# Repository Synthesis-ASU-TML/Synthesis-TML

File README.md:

Synthesis
=========

TML members share golden cutting edge paradigm shifting crisp optimized wonderful code with select lucky fellas at the synthesis center at asu arizona.

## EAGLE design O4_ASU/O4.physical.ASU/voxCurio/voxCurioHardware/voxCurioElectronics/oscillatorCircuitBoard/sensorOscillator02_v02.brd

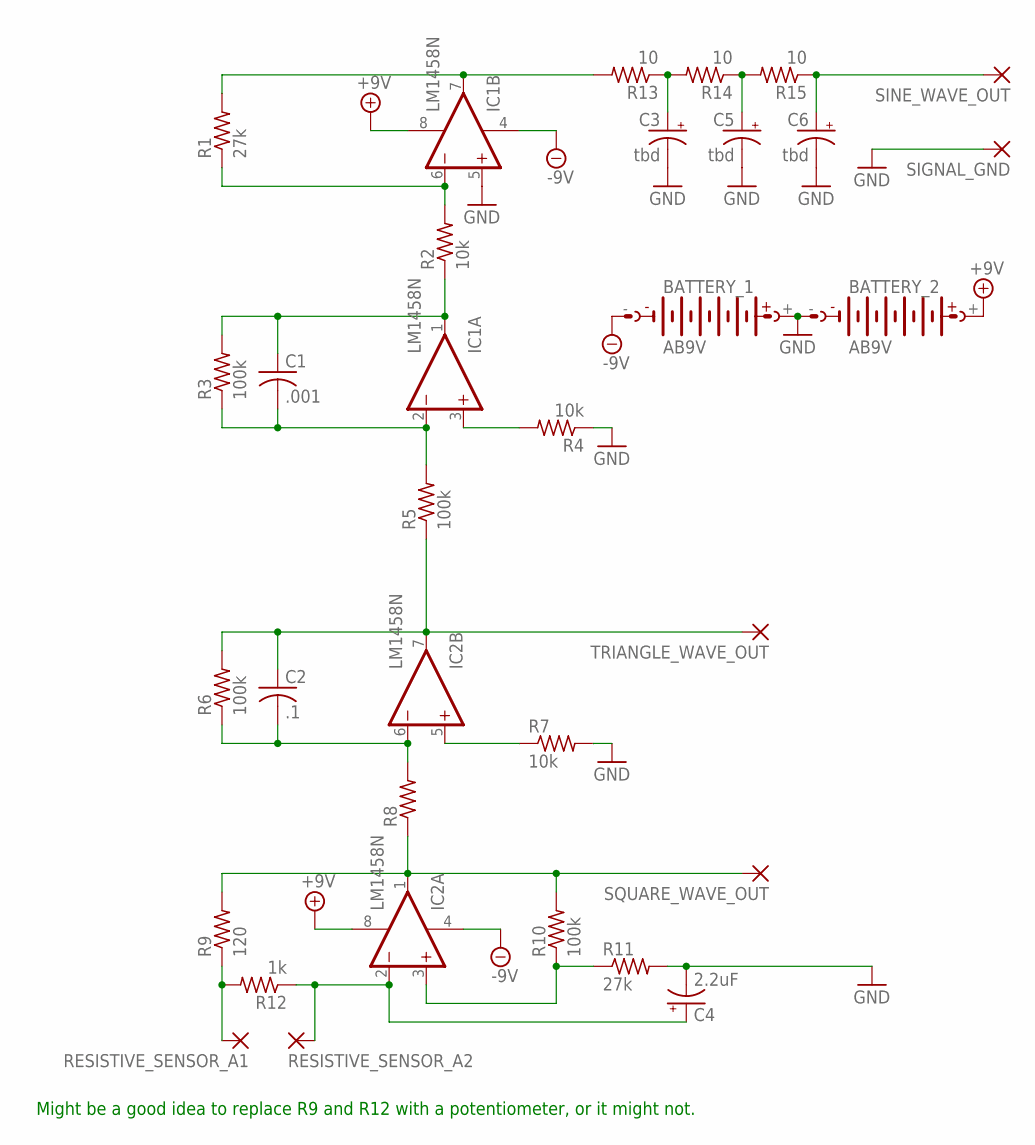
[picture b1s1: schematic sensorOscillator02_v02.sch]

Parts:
BATTERY_1, BATTERY_2: AB9V
C1: .001; C075-063X106
C2: .1; C075-063X106
C3, C5, C6: tbd; E5-5
C4: 2.2uF; E5-5
IC1, IC2: LM1458N; DIL08
R1, R11: 27k; 0411/12
R2, R4, R7: 10k; 0411/12
R3, R5, R6, R10: 100k; 0411/12
R8: R-US_0411/12; 0411/12
R9: 120; 0411/12
R12: 1k; 0411/12
R13, R14, R15: 10; 0411/12
RESISTIVE_SENSOR_A1, RESISTIVE_SENSOR_A2: 3,81/1,3
SIGNAL_GND: 3,81/1,3
SINE_WAVE_OUT: 3,81/1,3
SQUARE_WAVE_OUT: 3,81/1,3
TRIANGLE_WAVE_OUT: 3,81/1,3

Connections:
+9V: BATTERY_2.+, IC1.8 (V+), IC2.8 (V+)
-9V: BATTERY_1.-, IC1.4 (V-), IC2.4 (V-)
GND: BATTERY_1.+, BATTERY_2.-, C3.-, C4.-, C5.-, C6.-, IC1.5 (+IN), R4.1, R7.2, R11.2, SIGNAL_GND.1
unnamed: IC1.6 (-IN), R1.1, R2.2
unnamed: C1.1, IC1.1 (OUT), R2.1, R3.2
unnamed: IC1.7 (OUT), R1.2, R13.2
unnamed: C1.2, IC1.2 (-IN), R3.1, R5.2
unnamed: IC1.3 (+IN), R4.2
unnamed: C2.1, IC2.7 (OUT), R5.1, R6.2, TRIANGLE_WAVE_OUT.1
unnamed: C2.2, IC2.6 (-IN), R6.1, R8.2
unnamed: C3.+, R13.1, R14.2
unnamed: IC2.1 (OUT), R8.1, R9.2, R10.2, SQUARE_WAVE_OUT.1
unnamed: IC2.3 (+IN), R10.1, R11.1
unnamed: R9.1, R12.2, RESISTIVE_SENSOR_A1.1
unnamed: C4.+, IC2.2 (-IN), R12.1, RESISTIVE_SENSOR_A2.1
unnamed: IC2.5 (+IN), R7.1
unnamed: C5.+, R14.1, R15.2
unnamed: C6.+, R15.1, SINE_WAVE_OUT.1

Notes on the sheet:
Might be a good idea to replace R9 and R12 with a potentiometer, or it might not.

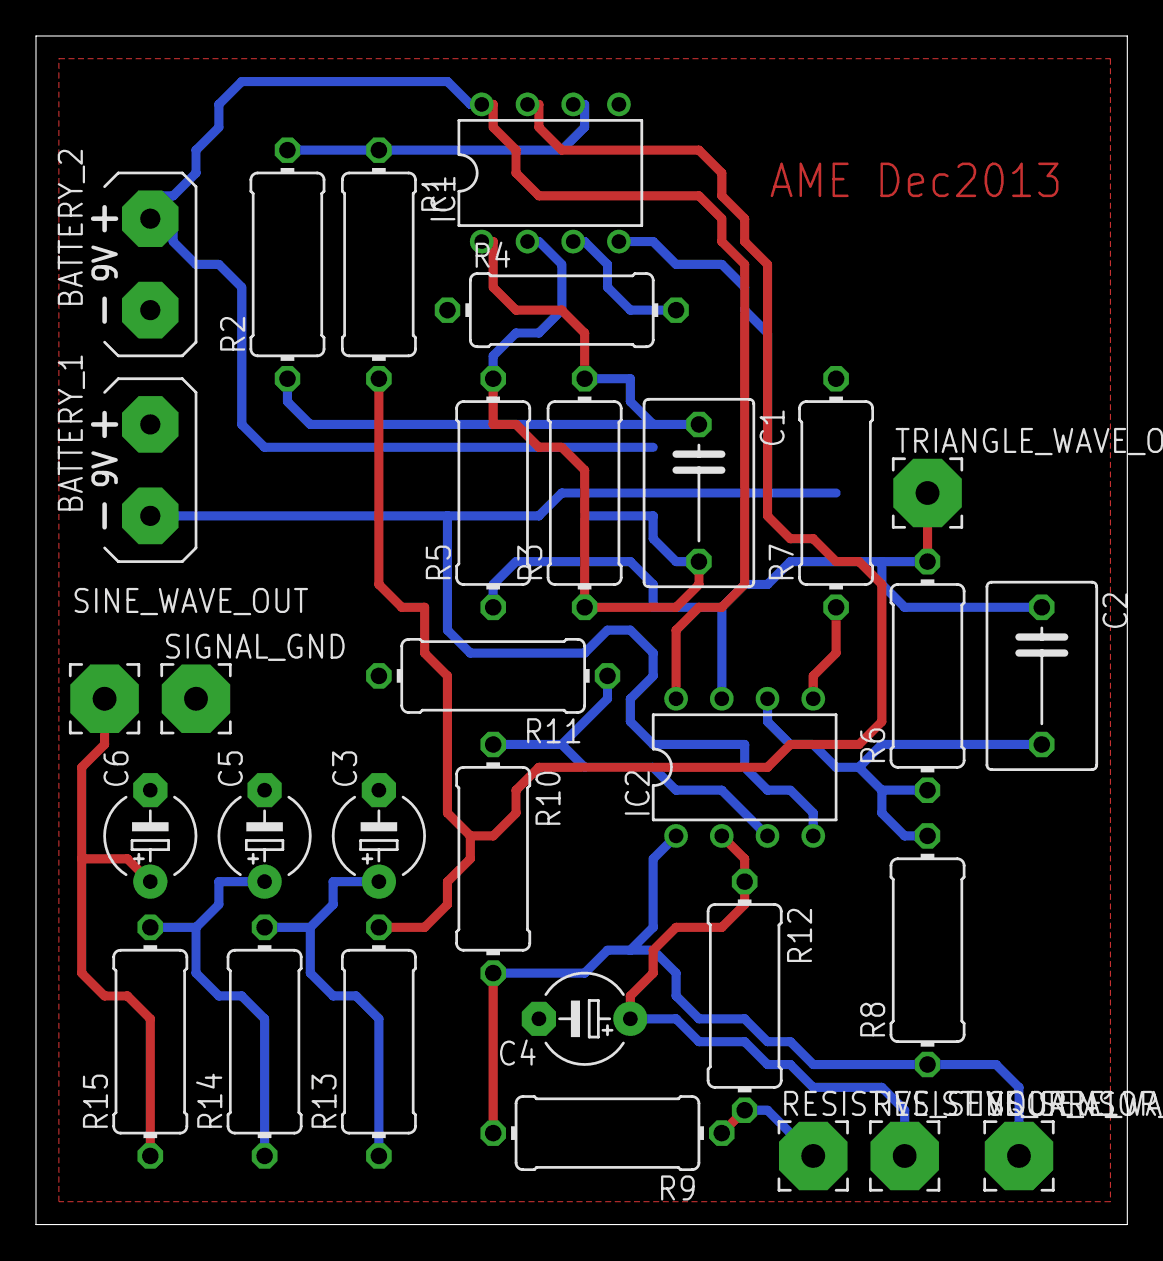
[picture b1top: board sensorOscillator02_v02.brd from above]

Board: 2 copper layers, 60.6 x 66.0 mm, 31 parts (0 on the bottom side), 18 nets.

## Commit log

2014-02-22 first push
    Da good sound
2014-02-22 initial push - o4.net.ASU
    initial push of o4.network objects
2014-02-24 initial push - O4.lighting.ASU
    first push of O4 Lighting Tools
2014-02-24 initial push - o4.rhyth_abs
    first push of o4.rhyth tools
2014-02-25 changes to dmx and rhythm
    -updated rhythm tools to output out both time and data
    -added tml.dmx_env
    -added missing dependencies
2014-02-25 changes to dmx library
2014-02-25 o4.video - messsssy alpha
2014-02-25 fixed jmod.gl.tp.slide%
2014-02-27 updates to lighting
    updates to lighting
2014-02-27 updates to rhythm and read me
    updates to rhythm and read me
2014-02-27 changes to asu mira
    changes to asu mira
2014-02-28 update to o4.lighting.asu
    update to o4.lighting.asu
2014-02-28 o4 lighting asu - added wifi note
    o4 lighting asu - added wifi note
2014-02-28 updates...
2014-03-03 o4Sound
2014-03-03 mira
2014-03-03 o4 rhyth abs - rhyth shoes
    o4 rhyth abs - rhyth shoes
2014-03-04 Working on help files.
2014-03-06 Create gh-pages branch via GitHub
2014-03-06 Revising particleFlow help file.
2014-03-06 bcf200
2014-03-06 changes for simplification of the installation process
2014-03-06 change
2014-03-06 particleFlow help updates
2014-03-06 particleFlow help file development.
2014-03-06 move rhyth-overview to correct folder
    move rhyth-overview to correct folder
2014-03-07 working on particleFlow help
2014-03-07 Optimizations for Easier Installation of O4
2014-03-08 All video instruments and modules are added now
2014-03-08 sync
2014-03-10 more editing on particleFlow help
2014-05-27 Updates to repos shader, fluids UI and particles
    See title
2014-06-29 changes to tml.dmx_nodes
    changes to tml.dmx_nodes
2014-06-30 changes to tml.dmx_matrix
    changes to tml.dmx_matrix
2014-07-23 adding patch for 390 lighting
2014-08-18 updates to tml.dmx
    new list input function to tml.dmx_ch, new wrapping function to
    tml.dmx_op, new example: tml.dmx_wrappingExample, updated help files
2014-10-10 Added jmod.syhonserver% and jmod.syphonclient%
2014-10-10 Added arduino code for cameraProjectorRobot
    first add of this code.
2014-10-11 First pass of syphonclient%/server% help.
2014-10-11 Added max code for cameraProjectorRobot
    Still rough and relatively uncommented, but improving… (first add of
    this file)
2014-10-11 Updating Syphonclient/server help files
2014-10-14 gsges
2014-10-14 sees.. ruined a perfect patch
2014-10-15 Mira changes
2014-10-15 Bug fix in jmod.syphonclient%
    Sending “set” message to the [umenu] listing available servers in both
    the jmod and jalg was causing unreliable behaviour. Removed the “set”
    in the jmod.
2014-10-15 Added preset file for jmod.syphonserver%
2014-10-15 syphonclient% and server% are better at auto-init
    Turned on @repetitions/allow 1 in the [jcom.return] used to populate
    the server [umenu] in [jmod.syphonclient%], so that now servers with
    identical names will show up. Added a [jcom.init] to
    [jmod.syphonserver%] so that the module announces itself with its
    default server name as soon as it’s loaded, and is automatically found
    by [jmod.syphonclient%].
2014-10-16 More tweaks to syphon client and server
    Added note about dependancy on Syphon for Jitter and link. Removed
    fullscreen toggle from help file (trapped user in fullscreen, requiring
    force quit of Max).
2014-10-17 Fixing Git-introduced errors in jmod.syphonclient%
    Deleted “Updated upstream” and “Stashed changes” tags
2014-10-25 compute correlation across two time series
    Michael Krzyzaniak <mkrzyzan@asu.edu>, PhD in MAS, AME, ASU
2014-10-29 Updated to demonstrate complex signal correlation
2014-10-29 Added preset files to some of the Jamoma shaders.
2014-10-30 Partial bug fix to vipr.tx
    Vipr.tx is now better at not glitching out when input resolution changes
2014-11-04 Added video dependencies
    Syphon for Jitter, vipr, Syphon Camera
2014-11-04 Spidahwebz
    Updated jmod.gl.gn.spiderweb% to run without needing input, and to
    automatically map xy offset coordinates to resolution.
2014-11-04 Revising jmod.gl.gn.gloop%
2014-11-05 Finished adding presets for Jamomized C74 shaders
2014-11-06 Added vipr transmitter and receiver
2014-11-07 Added jmod.gl.ab.spotmask, fixed alphamix
    Alphamix now defaults to blend_mode 6 6
2014-11-10 Correlation v 2.0
    Implemented efficient hypercomplex (quaternion) correlation. Included
    example Max patches for real, complex, and hypercomplex signals.
2014-11-10 rhyth abs 2.0 + video/osc sync tools
    major overhaul of rhythm toolkit + new video/osc sync based on o.table
    object
2014-11-10 moving rhyth.overview
2014-11-10 resized objects
    resized rhyth.phrase + rhyth.play
2014-11-10 Rotate and spotmask, syphonclient, particles
2014-11-12 Updates to particles
2014-11-12 Fixing vipr.tx again
2014-11-12 Table of Content 2.0
    All ToC applications have been revised, more functionality packaged
    into Jamoma modules.
2014-11-12 updates to rhythm tools
2014-11-12 Updated ToC 2.0
    Added particle direction control to particles, preview selection to
    camera.
2014-11-16 fix path bugs in o4.track
2014-11-16 fix path bugs - rhythm tools
2014-11-17 major changes to rhyth.store, 2 more examples
2014-11-17 updates to rhyth.store
2014-11-19 add rhyth.coprrelation
2014-11-23 LRR door files
    Lighting and Rhythm residency Patches and related files
2014-12-10 syphon client debug for 1934
2014-12-10 Added ToC Main crash detection app, lighting app
    Also some preset updates
2014-12-16 re-git this sound
2014-12-16 re-sonify + no improv
2014-12-21 Update
    Partially fixed quaternion correlation. The result is now correct but
    is implemented using a slow, brute-force algorithm. This algorithm
    takes about three times longer to rum for 64 sample windows, and the
    discrepancy grows exponentially with input size. An untested C-Language
    implementation is included just for funzies.
2015-01-21 TGVU/eerm
    Posting the tgvu-code folder, including eery.
2015-01-28 Max/MSP implementation of Vinay and Kuldeep's work
    Phase space reconstruction for periodic movement, and Recurrence plots.
2015-02-04 current portal codes for ame buildings
    current portal codes for ame buildings
2015-02-10 LRRdoor update and LED lighting controller
    This change includes the latest code for Lighting &Rhythm Residency
    door portal with integrated kinect view controller. It also has the
    latest lighting controller which includes the 3x3 RGB LED lights.
2015-03-26 Added cprMoon code
    Camera Projector Robot (CPR) code (Moon application) by Byron Lahey,
    first added to archive.
2015-03-26 Added cprMoon code
2015-03-26 added camera projector robot (CPR) microcontroller code
2015-03-26 added camera projector robot (CPR) hardware files
    created in Autodesk Inventor, cut on laser cutter.
2015-03-26 added OctoBoto hardware files
    Also moved previously existing octoboticus folder into newly created
    octoBoto folder
2015-03-26 added octoBoto files for laser cutting and maxpat
2015-03-26 added voxCurio hardware and code files
2015-03-27 added max abstractions and externals
2015-04-02 Added shader folder.
2015-04-24 portal code updates
    updates to Stauffer reception which includes - stream to any address
    option and fade recording
    to clip instead of black.
    New Gallery portal code is also added.
2015-04-24 stage portal code update
    added a revised Istage patch that streams Istage images to up to 6
    individually selectable destinations.
2015-04-28 storytelling_v1.0 first upload
    All storytelling_v1.0 files. Includes standalones, max patches and all
    required max libraries. There may be issues with the
    STS_PanicButton.app and the tmlSpeechClusters.app that will require
    revisions soon.
2015-04-29 ElasticTime added to O4.video
    This is a new addition of the ElasticTime code to the O4.video section
    of the synthesis repository
2015-04-30 O4.ASU documentation and required files for cprMoon
    Vision, lab technical documents, research goals; simplemessageSystem
    folder required for cprMoon functionality
2015-05-04 Changes to /math
    New correlation code (new approach to normalization) with audio
    synthesizer and simple demo.
2015-05-05 just sync with remote master
2015-05-21 sync with tgvu changes
    commit and sync to accept tgvu code changes
2015-07-30 Istage riser diagram added
    Istage_Riser.pdf prepared by Ian Shelansky added to the document
    section
2015-09-09 TGVU
2015-09-09 Syphonclient% patch
    Set jcom.return to @type string to prevent it from causing crashes.
2015-11-14 trying to sync
    problem with fluids_membrane/*
2016-11-26 julian stein 11/21/2016
    irvine embodied encounters
